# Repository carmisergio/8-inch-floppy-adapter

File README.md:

# 8-inch floppy drive adapter board
This boards allows 8-inch floppy drives to work on normal PC FDCs, or particularly a [Greaseweazle](https://github.com/keirf/greaseweazle)

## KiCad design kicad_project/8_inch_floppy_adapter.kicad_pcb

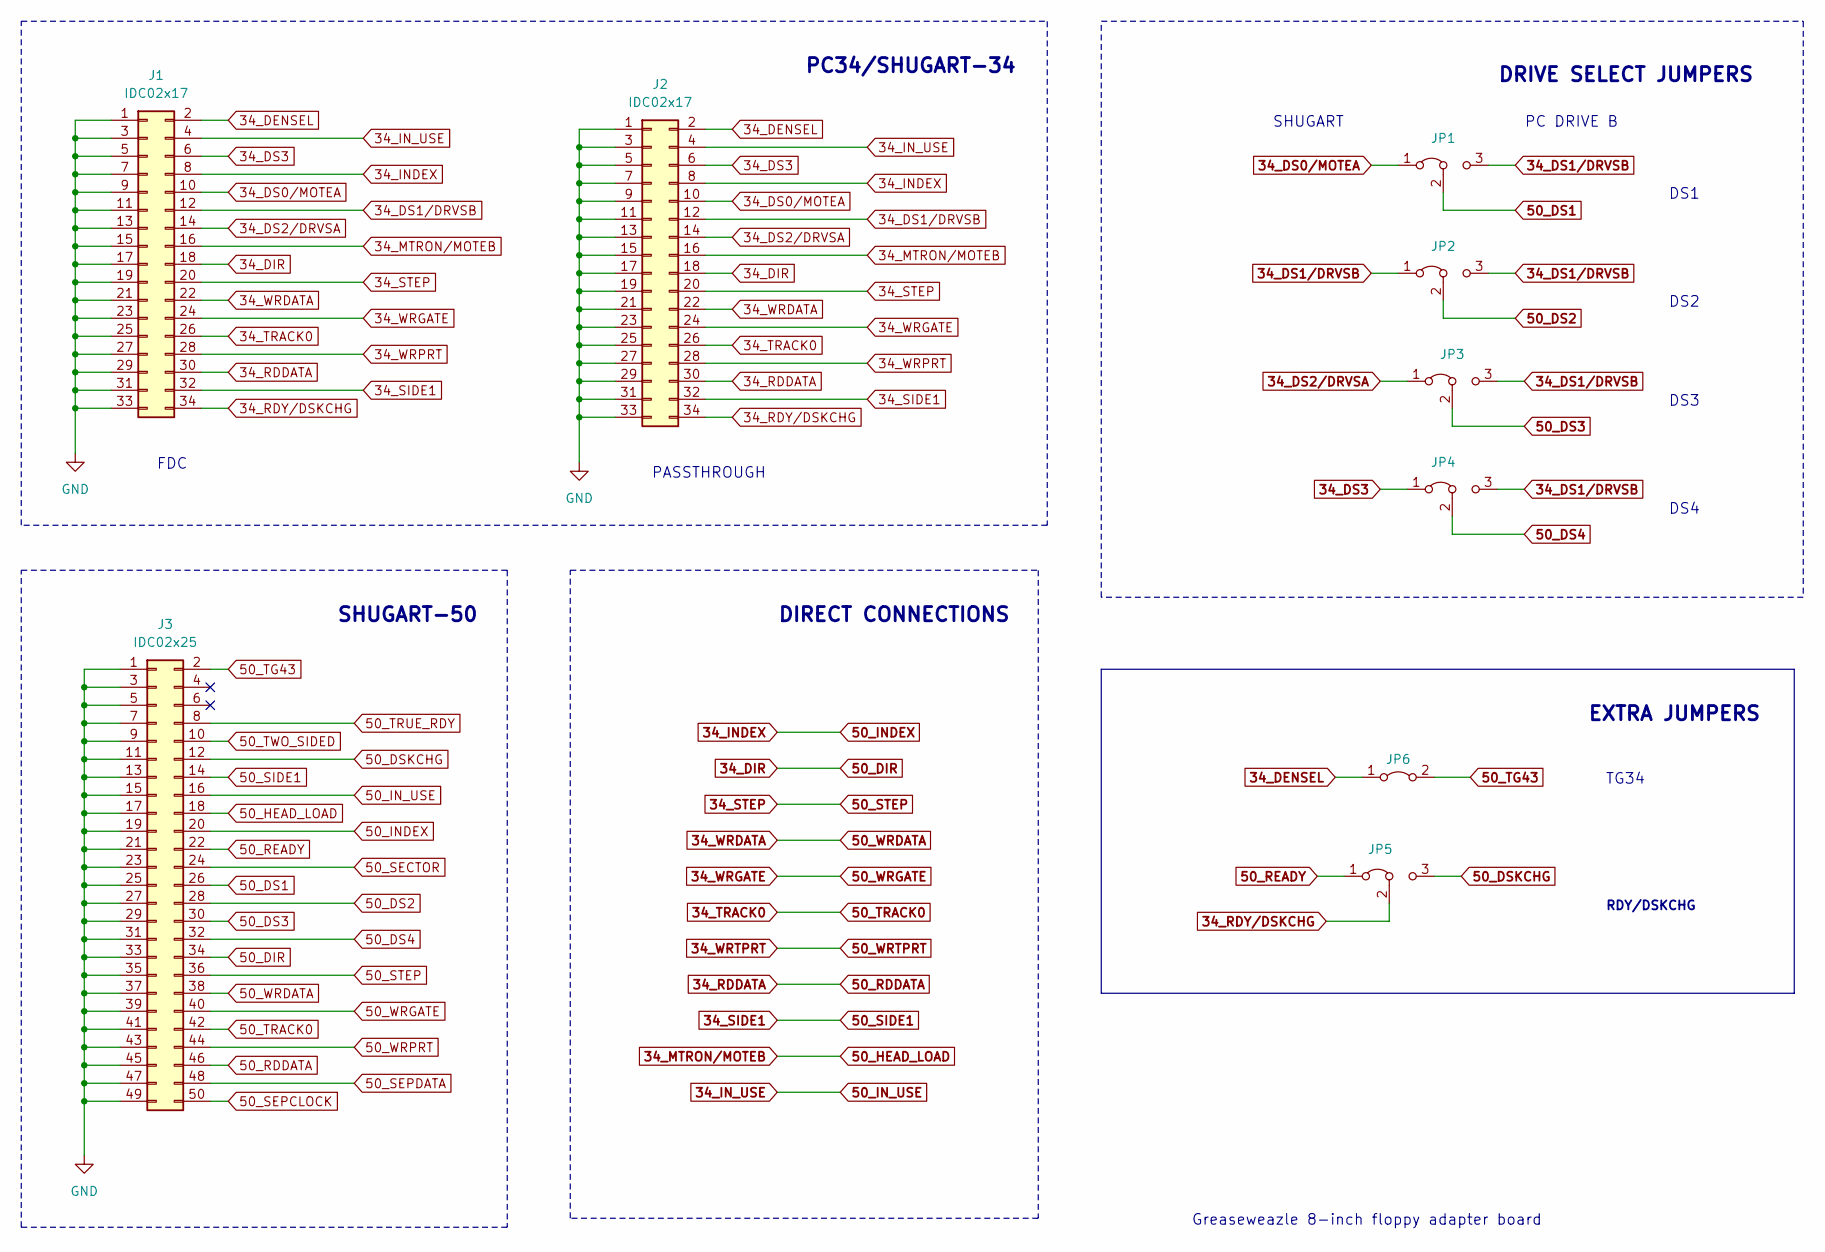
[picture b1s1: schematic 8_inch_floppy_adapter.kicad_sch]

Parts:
J1, J2: IDC02x17; IDC-Header_2x17_P2.54mm_Vertical
J3: IDC02x25; IDC-Header_2x25_P2.54mm_Vertical
JP1, JP2, JP3, JP4, JP5: Jumper_3_Bridged12; PinHeader_1x03_P2.54mm_Vertical
JP6: Jumper_2_Bridged; PinHeader_1x02_P2.54mm_Vertical

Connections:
34_DENSEL: J1.2, J2.2, JP6.1 (A)
34_DIR: J1.18, J2.18, J3.34
34_DS0/MOTEA: J1.10, J2.10, JP1.1 (A)
34_DS1/DRVSB: J1.12, J2.12, JP1.3 (B), JP2.1 (A), JP2.3 (B), JP3.3 (B), JP4.3 (B)
34_DS2/DRVSA: J1.14, J2.14, JP3.1 (A)
34_DS3: J1.6, J2.6, JP4.1 (A)
34_INDEX: J1.8, J2.8, J3.20
34_IN_USE: J1.4, J2.4, J3.16
34_MTRON/MOTEB: J1.16, J2.16, J3.18
34_RDDATA: J1.30, J2.30, J3.46
34_RDY/DSKCHG: J1.34, J2.34, JP5.2 (C)
34_SIDE1: J1.32, J2.32, J3.14
34_STEP: J1.20, J2.20, J3.36
34_TRACK0: J1.26, J2.26, J3.42
34_WRDATA: J1.22, J2.22, J3.38
34_WRGATE: J1.24, J2.24, J3.40
34_WRPRT: J1.28, J2.28
50_DS1: J3.26, JP1.2 (C)
50_DS2: J3.28, JP2.2 (C)
50_DS3: J3.30, JP3.2 (C)
50_DS4: J3.32, JP4.2 (C)
50_DSKCHG: J3.12, JP5.3 (B)
50_READY: J3.22, JP5.1 (A)
50_SECTOR: J3.24
50_SEPCLOCK: J3.50
50_SEPDATA: J3.48
50_TG43: J3.2, JP6.2 (B)
50_TRUE_RDY: J3.8
50_TWO_SIDED: J3.10
50_WRPRT: J3.44
GND: J1.1, J1.3, J1.5, J1.7, J1.9, J1.11, J1.13, J1.15, J1.17, J1.19, J1.21, J1.23, J1.25, J1.27, J1.29, J1.31, J1.33, J2.1, J2.3, J2.5, J2.7, J2.9, J2.11, J2.13, J2.15, J2.17, J2.19, J2.21, J2.23, J2.25, J2.27, J2.29, J2.31, J2.33, J3.1, J3.3, J3.5, J3.7, J3.9, J3.11, J3.13, J3.15, J3.17, J3.19, J3.21, J3.23, J3.25, J3.27, J3.29, J3.31, J3.33, J3.35, J3.37, J3.39, J3.41, J3.43, J3.45, J3.47, J3.49

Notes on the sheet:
PC34/SHUGART-34
DS2
SHUGART
DS3
DRIVE SELECT JUMPERS
PC DRIVE B
DS4
DIRECT CONNECTIONS
FDC
DS1
RDY/DSKCHG
TG34
Greaseweazle 8-inch floppy adapter board
SHUGART-50
PASSTHROUGH
EXTRA JUMPERS

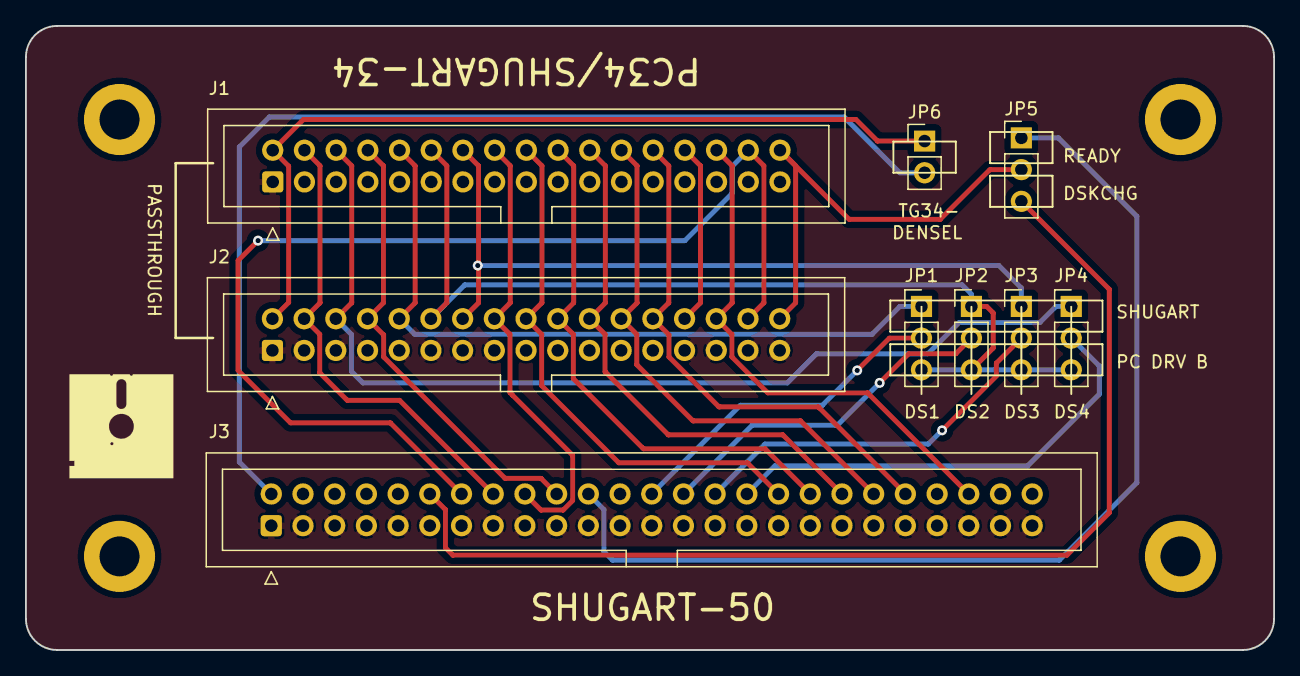
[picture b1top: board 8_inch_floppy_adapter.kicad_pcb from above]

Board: 2 copper layers, 100.0 x 50.0 mm, 9 parts (0 on the bottom side), 25 nets.

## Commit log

2024-02-11 PCB Version 1
2024-04-14 Refine routing
2024-07-28 Update makefile
